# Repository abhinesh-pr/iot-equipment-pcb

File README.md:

View this project on [CADLAB.io](https://cadlab.io/project/29129). 

# iot-equipment-pcb

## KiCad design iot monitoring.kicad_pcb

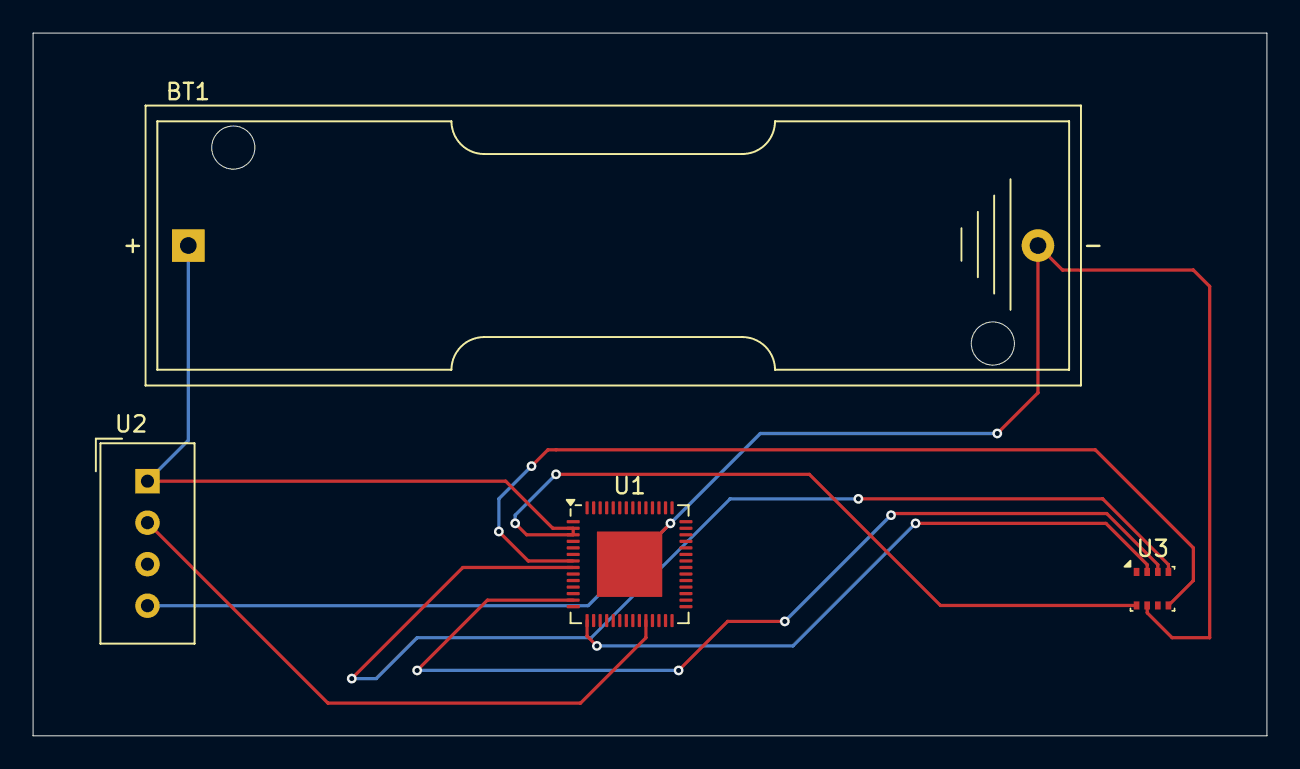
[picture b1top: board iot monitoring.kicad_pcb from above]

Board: 2 copper layers, 75.5 x 43.0 mm, 4 parts (0 on the bottom side), 7 nets.

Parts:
BT1: Battery_Cell; BatteryHolder_Keystone_2460_1xAA
U1: ESP32-S3; QFN-56-1EP_7x7mm_P0.4mm_EP4x4mm
U2: DHT11; Aosong_DHT11_5.5x12.0_P2.54mm
U3: BME280; Bosch_LGA-8_2.5x2.5mm_P0.65mm_ClockwisePinNumbering

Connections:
GND: BT1.2 (-), U1.57 (GND), U2.4 (GND), U3.7 (GND)
unnamed: BT1.1 (+), U1.2 (VDD3P3), U1.3 (VDD3P3), U2.1 (VDD), U3.8 (VDD)
unnamed: U1.7 (GPIO2), U3.5 (SDO)
unnamed: U1.8 (GPIO3), U3.4 (SCK)
unnamed: U1.13 (GPIO8), U3.3 (SDI)
unnamed: U1.15 (GPIO10), U3.2 (CSB)
unnamed: U1.24 (GPIO18), U2.2 (DATA)

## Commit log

2025-04-02 Init
2025-04-02 Backlink to CADLAB.io has been added.
